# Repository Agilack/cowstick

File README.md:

# Cowstick

The goal of Cowstick project is to create usefull tools for microcontroller
and FPGA development, for example JTAG/SWD probes, serial port adapter ...
This tools are not revolutionnary in their functions but offer a more
user-friendly approach based on network communication.

## usbkey-ios

This is the first member of cowstick familly. At this time, this key is only
a proof of concept. It contains a microcontroller with USB interface, and
many configurable IOs.

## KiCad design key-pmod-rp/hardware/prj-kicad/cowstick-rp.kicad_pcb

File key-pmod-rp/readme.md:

PMOD usbkey
===========

This usb-key is part of cowstick boards family and offer a compact PMOD host
interface. It can be used to test or use most 3,3V PMOD devices, for other
power supplies, a level translator should be used.

For the moment, this module is not supported by cowlab but will be added
soon.

CAD source
----------

This board has been designed using KiCad EDA (version 6). All sources files
(schematics, routing, ...) are available into the `hardware/prj-kicad` folder.

<table>
<tr>
<td></td>
<td></td>
</tr>
<tr>
<td>Fig1: Preview of the KiCad schematics</td>
<td>Fig2: Preview of the KiCad routing</td>
</tr>
</table>

License
-------

This project is OpenHardware. You can use (and/or modify) this project under
terms of the Creative Commons ShareAlike license (CC-by-SA).
See [hardware/LICENSE.md](hardware/LICENSE.md).

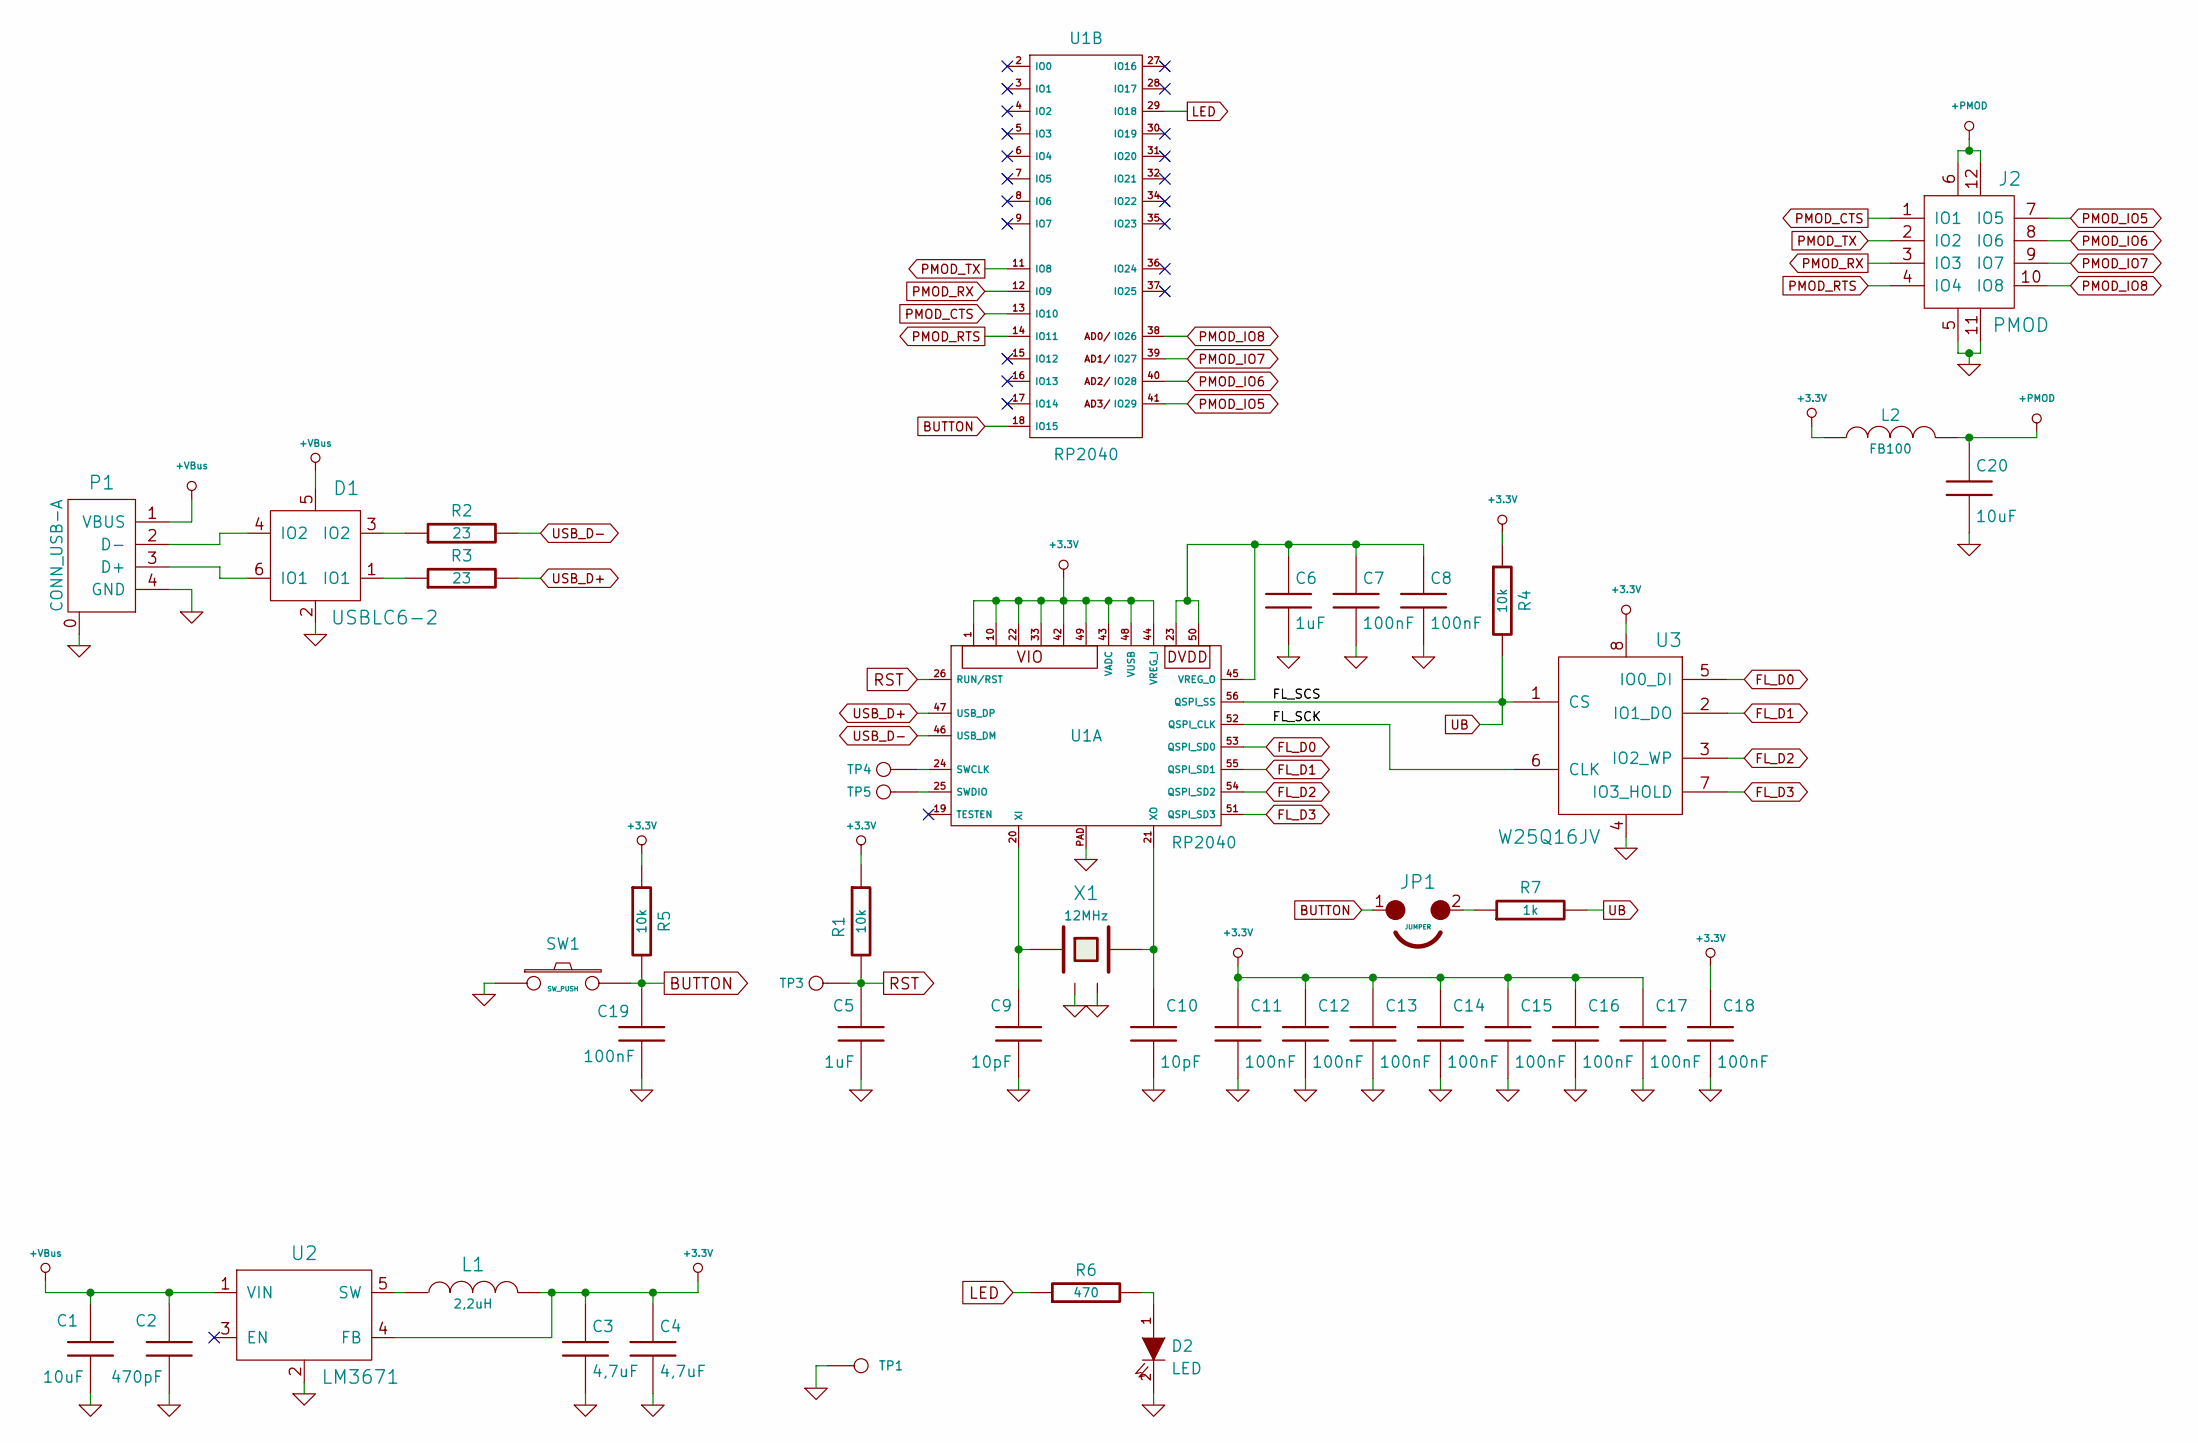
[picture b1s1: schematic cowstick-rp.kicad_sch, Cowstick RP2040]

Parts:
C1, C20: 10uF; SMD0805
C2: 470pF; SMD0603
C3, C4: 4,7uF; SMD0805
C5, C6: 1uF; SMD0603
C7, C8, C11, C12, C13, C14, C15, C16, C17, C18, C19: 100nF; SMD0603
C9, C10: 10pF; SMD0603
D1: USBLC6-2; SOT23-6
D2: LED; SMD0805
J2: PMOD; PMOD_SSW106-RA
JP1: JUMPER; TP_JP
L1: 2,2uH; I_CDRH2D14
L2: FB100; SMD0603
P1: CONN_USB-A; CONN_MC32604
R1, R4, R5: 10k; SMD0603
R2, R3: 23; SMD0603
R6: 470; SMD0603
R7: 1k; SMD0603
SW1: SW_PUSH; SW_436351045816
TP1, TP3, TP4, TP5: CONN_1; TP_SMD
U1: RP2040; QFN56
U2: LM3671; SOT23-5
U3: W25Q16JV; SOIC-8
X1: 12MHz; Q_3.2x2.5

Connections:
+3.3V: C3.1, C4.1, C11.1, C12.1, C13.1, C14.1, C15.1, C16.1, C17.1, C18.1, L1.2, L2.1, R1.1, R4.1, R5.1, U1.1, U1.10, U1.22, U1.33, U1.42, U1.43 (VADC), U1.44 (VREG_I), U1.48 (VUSB), U1.49, U2.4 (FB), U3.8
+PMOD: C20.1, J2.6, J2.12, L2.2
+VBus: C1.1, C2.1, D1.5, P1.1 (VBUS), U2.1 (VIN)
/FL_SCK: U1.52 (QSPI_CLK), U3.6 (CLK)
BUTTON: C19.1, JP1.1, R5.2, SW1.2, U1.18 (IO15)
FL_D0: U1.53 (QSPI_SD0), U3.5 (IO0_DI)
FL_D1: U1.55 (QSPI_SD1), U3.2 (IO1_DO)
FL_D2: U1.54 (QSPI_SD2), U3.3 (IO2_WP)
FL_D3: U1.51 (QSPI_SD3), U3.7 (IO3_HOLD)
GND: C1.2, C2.2, C3.2, C4.2, C5.2, C6.2, C7.2, C8.2, C9.2, C10.2, C11.2, C12.2, C13.2, C14.2, C15.2, C16.2, C17.2, C18.2, C19.2, C20.2, D1.2, D2.2 (K), J2.5, J2.11, P1.0, P1.4 (GND), SW1.1, TP1.1, U1.PAD, U2.2, U3.4, X1.2, X1.4
LED: R6.1, U1.29 (IO18)
unnamed: C6.1, C7.1, C8.1, U1.23, U1.45 (VREG_O), U1.50
unnamed: C9.1, U1.20 (XI), X1.1
unnamed: C10.1, U1.21 (XO), X1.3
unnamed: D1.1 (IO1), R3.1
unnamed: D1.3 (IO2), R2.1
unnamed: D1.4 (IO2), P1.2 (D-)
unnamed: D1.6 (IO1), P1.3 (D+)
unnamed: D2.1 (A), R6.2
unnamed: L1.1, U2.5 (SW)
unnamed: JP1.2, R7.1
unnamed: TP4.1, U1.24 (SWCLK)
unnamed: TP5.1, U1.25 (SWDIO)
PMOD_CTS: J2.1 (IO1), U1.13 (IO10)
PMOD_IO5: J2.7 (IO5), U1.41 (IO29)
PMOD_IO6: J2.8 (IO6), U1.40 (IO28)
PMOD_IO7: J2.9 (IO7), U1.39 (IO27)
PMOD_IO8: J2.10 (IO8), U1.38 (IO26)
PMOD_RTS: J2.4 (IO4), U1.14 (IO11)
PMOD_RX: J2.3 (IO3), U1.12 (IO9)
PMOD_TX: J2.2 (IO2), U1.11 (IO8)
RST: C5.1, R1.2, TP3.1, U1.26 (RUN/RST)
UB: R4.2, R7.2, U1.56 (QSPI_SS), U3.1 (CS)
USB_D+: R3.2, U1.47 (USB_DP)
USB_D-: R2.2, U1.46 (USB_DM)

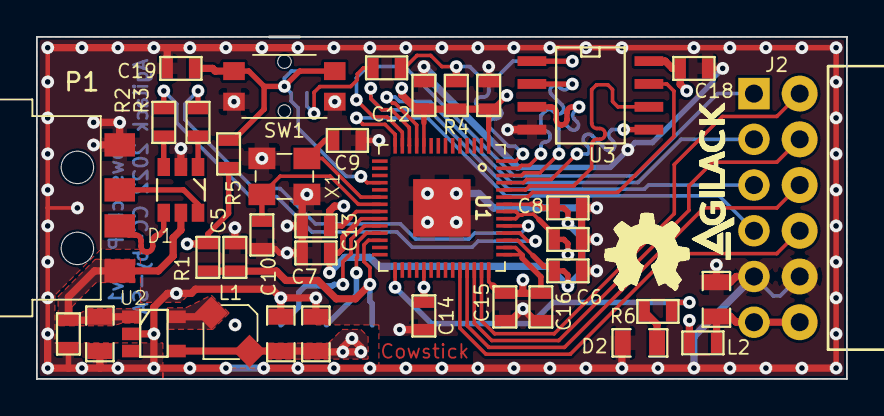
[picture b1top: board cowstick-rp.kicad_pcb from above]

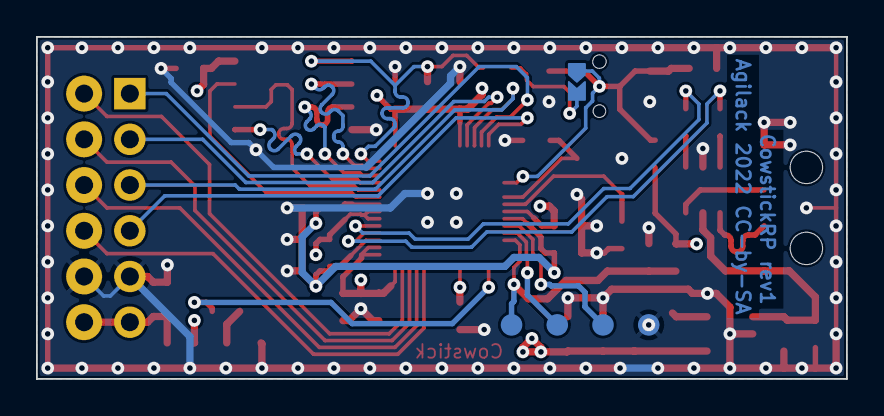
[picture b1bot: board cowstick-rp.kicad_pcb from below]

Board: 4 copper layers, 45.0 x 19.0 mm, 45 parts (5 on the bottom side), 35 nets.

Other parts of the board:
agilack-11.5: 450px; logo-agilack
ohw_logo: VAL**; logo-ohw

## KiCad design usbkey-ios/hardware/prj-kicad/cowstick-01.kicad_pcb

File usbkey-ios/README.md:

# Cowstick usbkey

This USB-key is part of the cowstick boards family. It is a very compact and
low-cost module that allow to connect and communicate with many serial ports
(like ICSP, JTAG, SPI, SWD, ...) over USB. This module can also be used with
cowlab tools to offer a user-friendly interface :)

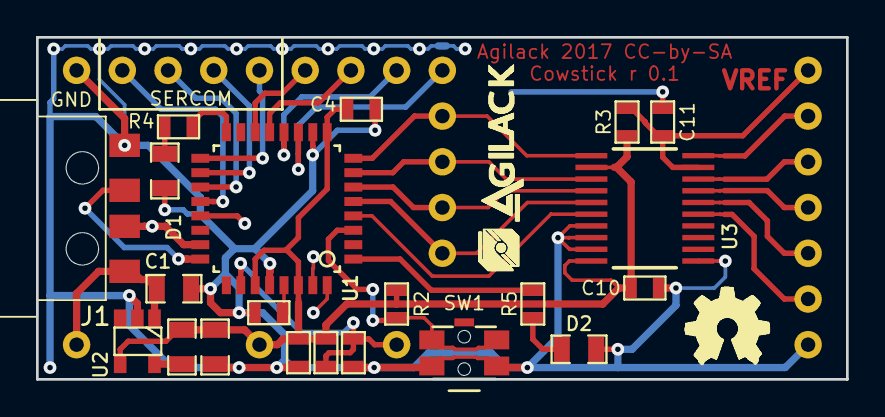
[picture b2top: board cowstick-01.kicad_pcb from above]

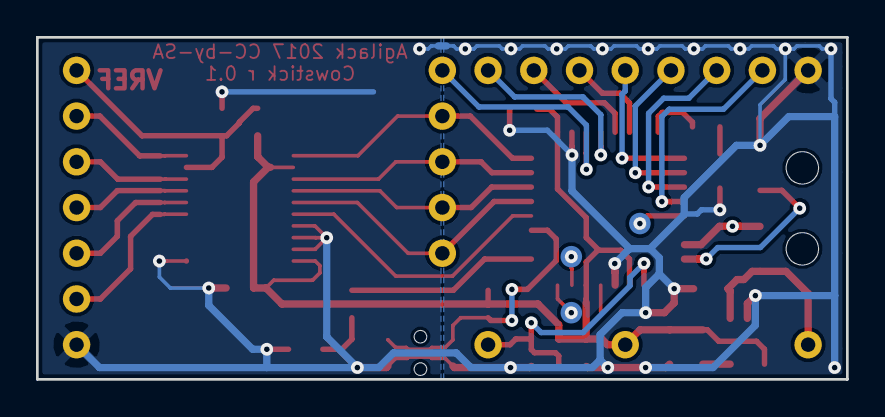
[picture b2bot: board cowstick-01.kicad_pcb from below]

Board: 2 copper layers, 45.0 x 19.0 mm, 49 parts (3 on the bottom side), 35 nets.

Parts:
C1, C2: 10uF; SMD0805
C3, C4, C10: 100nF; SMD0603
C5, C6: 1uF; SMD0603
C11: C; SMD0603
D1, D2: LED; SMD0805
EXT_1, EXT_2, EXT_3, EXT_4, EXT_6, EXT_7: CONN_1; TP
EXT_PWR0: CONN_1; TP
J1: CONN_USB-A; CONN_MC32604
L1: 2,2uH; SMD0805
P1, P2, P3, P4, P5, P6, P7, P8, P9, P10, P11, P12: CONN_1; TP
R1, R2: 10k; SMD0603
R3: 0; SMD0603
R4, R5: 1k; SMD0603
SW1: SW_PUSH; SW_PTS840
TP1, TP2, TP3, TP6: CONN_1; TP
TP4, TP5, TP7: CONN_1; TP_SMD
U1: ATSAMD21ExxA-Axx; TQFP32
U2: LM3671; SOT23-5
U3: TXS0108E-PW; TSSOP20
agilack-11.5: 450px; agilack-11.5
ohw_logo: VAL**; ohw-logo

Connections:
+3.3V: C2.1, C3.1, C4.1, C10.1, L1.2, R1.1, R2.1, R3.1, TP3.1, U1.9, U1.27, U1.30, U2.4, U3.2, U3.10
+VBus: C1.1, J1.1, TP2.1, U2.1
/SWCLK: TP4.1, U1.31
/SWDIO: TP5.1, U1.32
BUT: R2.2, SW1.1, U1.3
EXT_1: P9.1, U1.8, U3.1
EXT_2: P10.1, U1.7, U3.3
EXT_3: P11.1, U1.6, U3.4
EXT_4: P12.1, U1.5, U3.5
EXT_5: U1.4, U3.6
GND: C1.2, C2.2, C3.2, C4.2, C5.2, C6.2, C10.2, C11.2, D1.2, D2.2, EXT_7.1, J1.4, SW1.2, TP1.1, U1.10, U1.28, U2.2, U3.7, U3.8, U3.9, U3.11
LED: R4.2, U1.16
LED1: R5.2, U1.1
unnamed: C5.1, U1.29
unnamed: C11.1, EXT_PWR0.1, R3.2, U3.19
unnamed: D1.1, R4.1
unnamed: D2.1, R5.1
unnamed: EXT_1.1, U3.20
unnamed: EXT_2.1, U3.18
unnamed: EXT_3.1, U3.17
unnamed: EXT_4.1, U3.16
unnamed: EXT_6.1, U3.15
unnamed: J1.2, U1.23
unnamed: J1.3, U1.24
unnamed: L1.1, U2.5
unnamed: P1.1, U1.20
unnamed: P2.1, U1.19
unnamed: P3.1, U1.18
unnamed: P4.1, U1.17
unnamed: P5.1, U1.14
unnamed: P6.1, U1.13
unnamed: P7.1, U1.12
unnamed: P8.1, U1.11
unnamed: TP7.1, U1.21
RESET: C6.1, R1.2, TP6.1, U1.26

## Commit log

2017-05-09 = Create a new cowstick board : USBKEY-IOs - Add schematic and component library
2017-05-10 = Create footprint library and netlist
2017-05-11 = Add PCB routing (full version, not verified)
2017-05-11 = Add production files (gerber + drill)
2017-05-12 = ADD a unit-test for the status LED
2017-05-16 =UPD: update title, date and license into schematics and routing documents
2017-05-16 = ADD a unit-test for the UART
2017-05-17 = ADD: First pictures of the PCB :)
2017-05-18 = ADD: Picture of the PCB with components
2017-05-19 = ADD: Unit -tes for 3V3 power supply
2017-05-22 = ADD: Unit-test for status LED ... using TCC peripheral
2017-05-23 = ADD: Unit-test skeleton for USB device (now, only PLL config for 48MHz clock)
2017-05-24 = UPD: USB unit-test, config peripheral and attach to bus
2017-05-24 = UPD: USB unit-test, improve endpoint initial config, interrupt skeleton
2017-05-25 = UPD: improve endpoints handling (setup packets and GET_DESCRIPTOR request)
2017-05-25 = UPD: USB unit-test, move ep flags into more global ep structure, add function to handle out transfer
2017-05-25 UPD: USB unit-test, fix ep_status (clear on startup, ...) ; fix ep_desc
2017-05-26 = UPD: USB unit-test, improve interrupt handling, move GET_DESCRIPTOR case to a dedicated function
2017-05-26 = UPD: USB unit-test, improve enumeration (works \o/), fix GET/SET configuration,
2017-05-27 = DOC: USB unit-test, add comments and doxygen config to generate doc
2017-05-28 = DOC: update readme files (and fix small type in unit-test)
2017-05-29 = UPD: USB unit-test, Create a structure of device callbacks, add HID Report descriptor
2017-05-29 = UPD: USB unit-test, modify endpoint enable sequence, fix address of endpoint registers (other than EP0)
2017-05-30 = UPD: USB unit-test, process events on all ep (not only ep0) ; create a generic function tu transfer datas
2017-05-30 = UPD: USB unit-test, add mouse move commands into main loop (more realistic test)
2017-05-30 = UPD: USB unit-test, fix bug into DFLL init : use NVM calibration config for coarse parameter
2017-05-31 = UPD: USB unit-test, remove all hard-coded offsets of descriptors, add a function to find them
2017-05-31 = UPD: USB unit-test, move HID descriptor to the new descriptor "interface" array
2017-06-01 = UPD: Improve USB unit-test, use flag names (EP_ADDR), use usb_transfer instead of ep_transfer, fix control status for EP0
2017-06-01 = UPD: USB unit-test, another small update of DFLL clock config
2017-06-02 = DOC: USB unit-test, add comments and readme file
2017-06-05 = ADD: Skeleton of the cowstick bootloader
2017-06-05 UPD: import led status functions into bootloader (from unit-test)
2017-06-06 Update: import functions for pushbutton into bootloader
2017-06-06 Update bootloader: jump on main firmware or start bootloader according to button state at power-on
2017-06-07 Update USB unit-test: small cleanup (comments, unused variables)
2017-06-07 Bootloader: import USB stack from unit-test (only stack, no class or config)
2017-06-07 Bootloader: import uart functions (for auxilary debug port)
2017-09-12 Bootloader: increase clock frequency (48MHz for GCLK0, 8MHz for GCLK1)
2017-09-14 Bootloader: Improve USB ep transfer handling
2017-10-30 Bootloader: import USB-ECM basic layer
2017-10-31 Bootloader: Create a basic network layer and update ECM to allow data transfer
2017-11-01 Bootloader: add small network functions (htons, htonl)
2017-11-01 Bootloader: add functions to send network packets (net layer and USB ECM layer)
2017-11-02 Bootloader: add ARP support to network layer (only answer to req for board ip)
2017-11-07 Bootloader: add an IPv4 protocol module (only ip)
2017-11-08 Bootloader: add UDP network protocol to IPv4 module
2017-11-08 Bootloader: Small cleanup into IPv4 module and add API entry to init network
2017-11-09 Bootloader: add DHCP service. Offer IP (using BOOTP) to connected computer
2017-11-10 Bootloader: Improve DHCP server, handle dhcp extensions (and offer/ack)
2017-11-10 Bootloader: Small fix (number of interfaces into USB descriptors) and cleanups
2017-11-11 Bootloader: create a README file for bootloader
2017-11-20 Bootloader: add TCP network protocol to IPv4 module (incomplete/partial/beta!)
2017-11-21 Bootloader: improve TCP protocole handling - Connection handshake ; ack received datas
2017-11-21 Bootloader: improve TCP, handle connection closing
2017-11-22 Bootloader: add a 'service' structure to TCP to manage available servers
2017-11-22 Bootloader: minor TCP update, save a copy of network interface pointer into tcp connection structure
2017-11-23 Bootloader: fix some issues into tcp trasmit and close
2017-11-23 Bootloader: Clean. Use macro for debug message to remove them from firmware when not used
2017-11-24 Bootloader: improve TCP, add 'tx_more' method to send big buffers, all 'closed' method to notify service when connection closed
2017-11-24 Bootloader: update API entries to expose network functions
2017-12-06 Bootloader: add Flash module to handle internal memory erase/write
2017-12-07 Bootloader: small cleanup, use macro (conditional) for some debug messages
2017-12-07 Bootloader: improve internal libc, add function for strings (copy, len)
2017-12-08 Bootloader: add service to upgrade memory with a raw buffer sent over a TCP socket (direct-socket-upgrade)
2022-08-07 KeyPMOD: --=={ Create a new board "key-pmod-rp" }==--
2022-08-08 KeyPMOD: Improve PCB r1, add power supply (5V->3V3)
2022-08-09 KeyPMOD: Improve PCB r1, add RP2040 mcu (include crystal and decoupling caps)
2022-08-10 KeyPMOD: Add flash memory and USB protection. Design of board rev1 mostly finish
2022-08-11 KeyPMOD: Create production files for pcb rev1
2022-08-12 KeyPMOD: Create firmware skeleton, add basic driver for UART

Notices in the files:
key-pmod-rp/hardware/prj-kicad/cowstick-rp.kicad_pcb:
Agilack 2022 CC-by-SA
usbkey-ios/hardware/prj-kicad/cowstick-01.kicad_pcb:
License CC-by-SA 2.0
Agilack 2017 CC-by-SA
